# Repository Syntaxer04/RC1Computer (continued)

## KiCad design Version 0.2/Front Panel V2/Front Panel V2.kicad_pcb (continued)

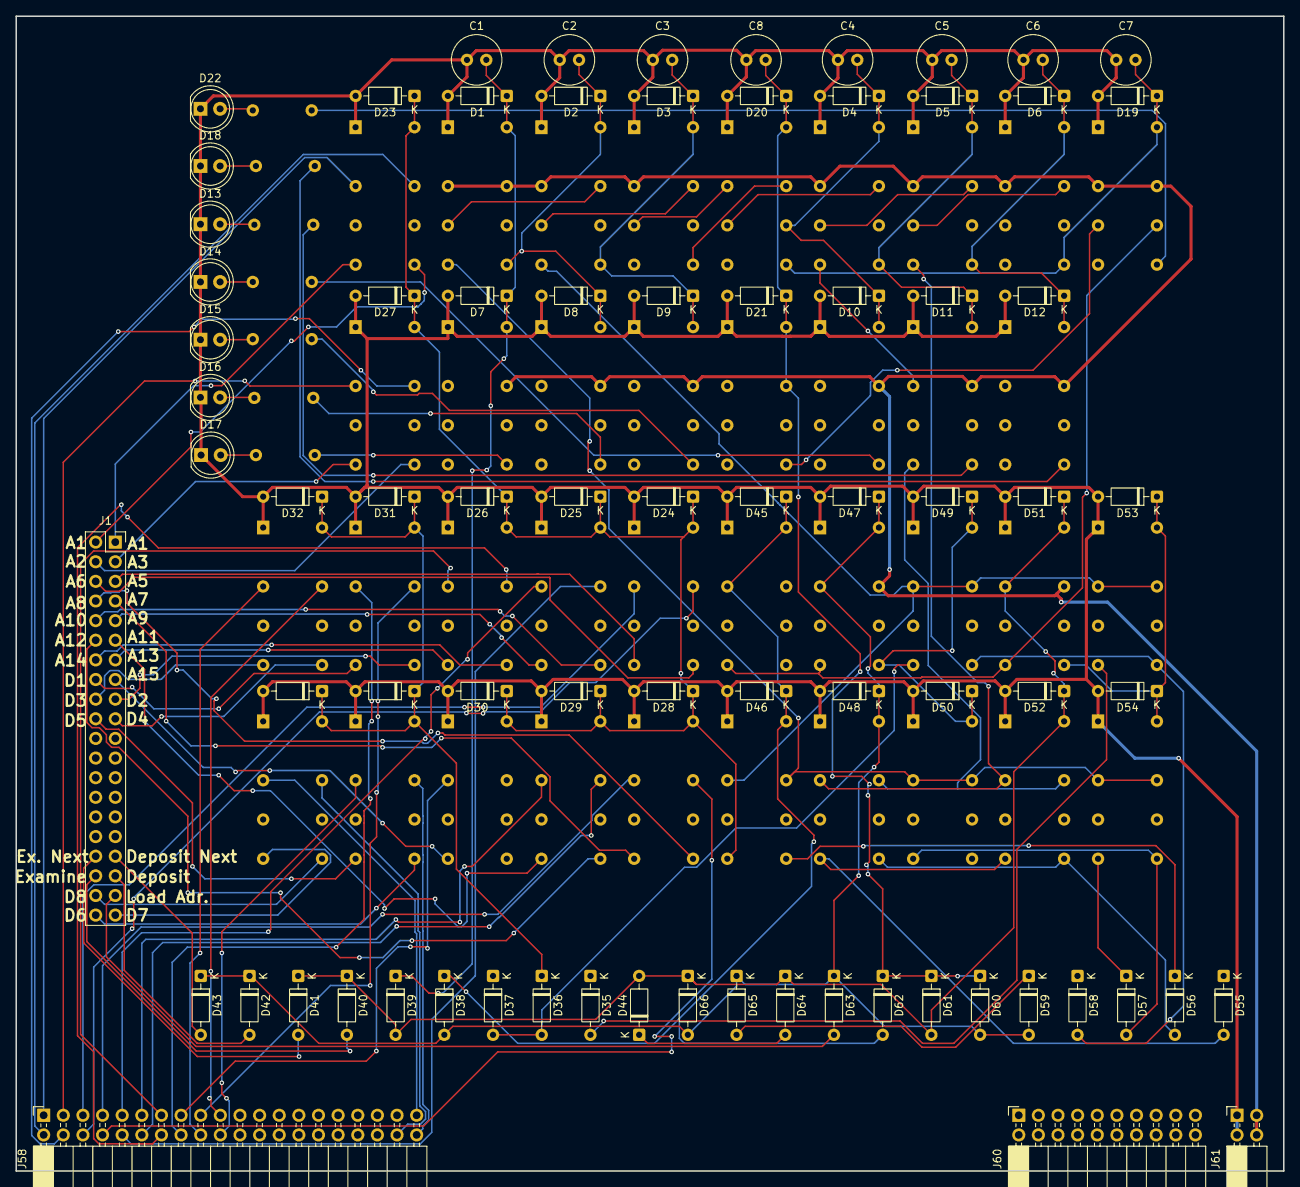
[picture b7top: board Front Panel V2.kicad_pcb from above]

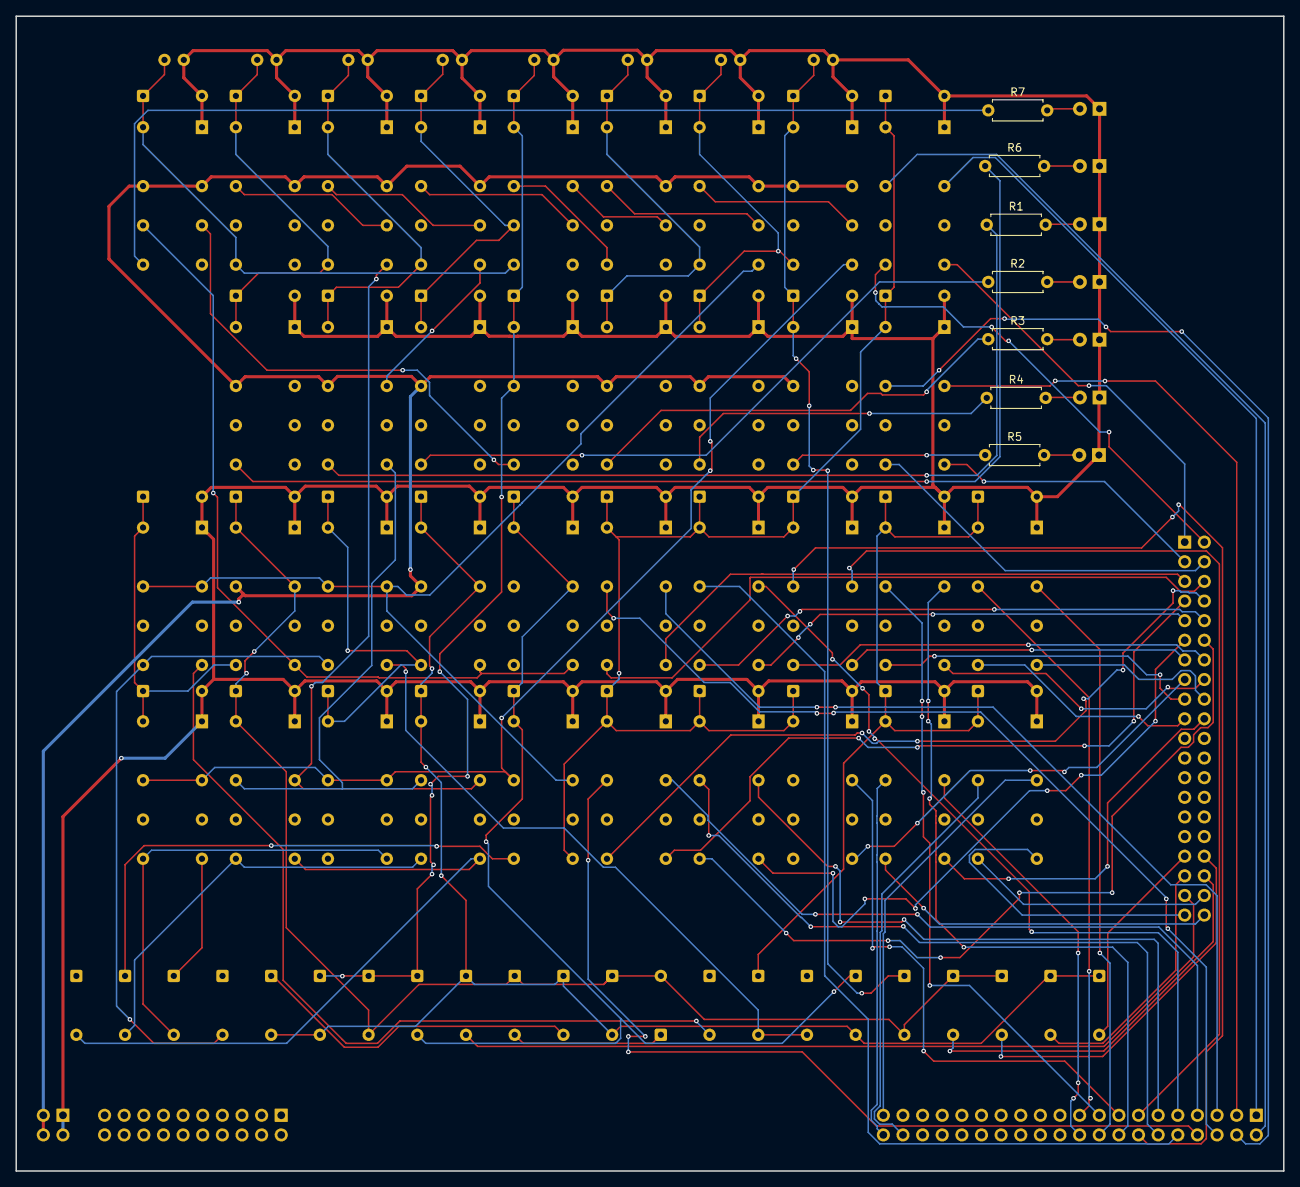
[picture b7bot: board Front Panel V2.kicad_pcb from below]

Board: 2 copper layers, 164.0 x 149.4 mm, 122 parts (7 on the bottom side), 106 nets.

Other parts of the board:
J60: Conn_02x10_Odd_Even; PinSocket_2x10_P2.54mm_Horizontal

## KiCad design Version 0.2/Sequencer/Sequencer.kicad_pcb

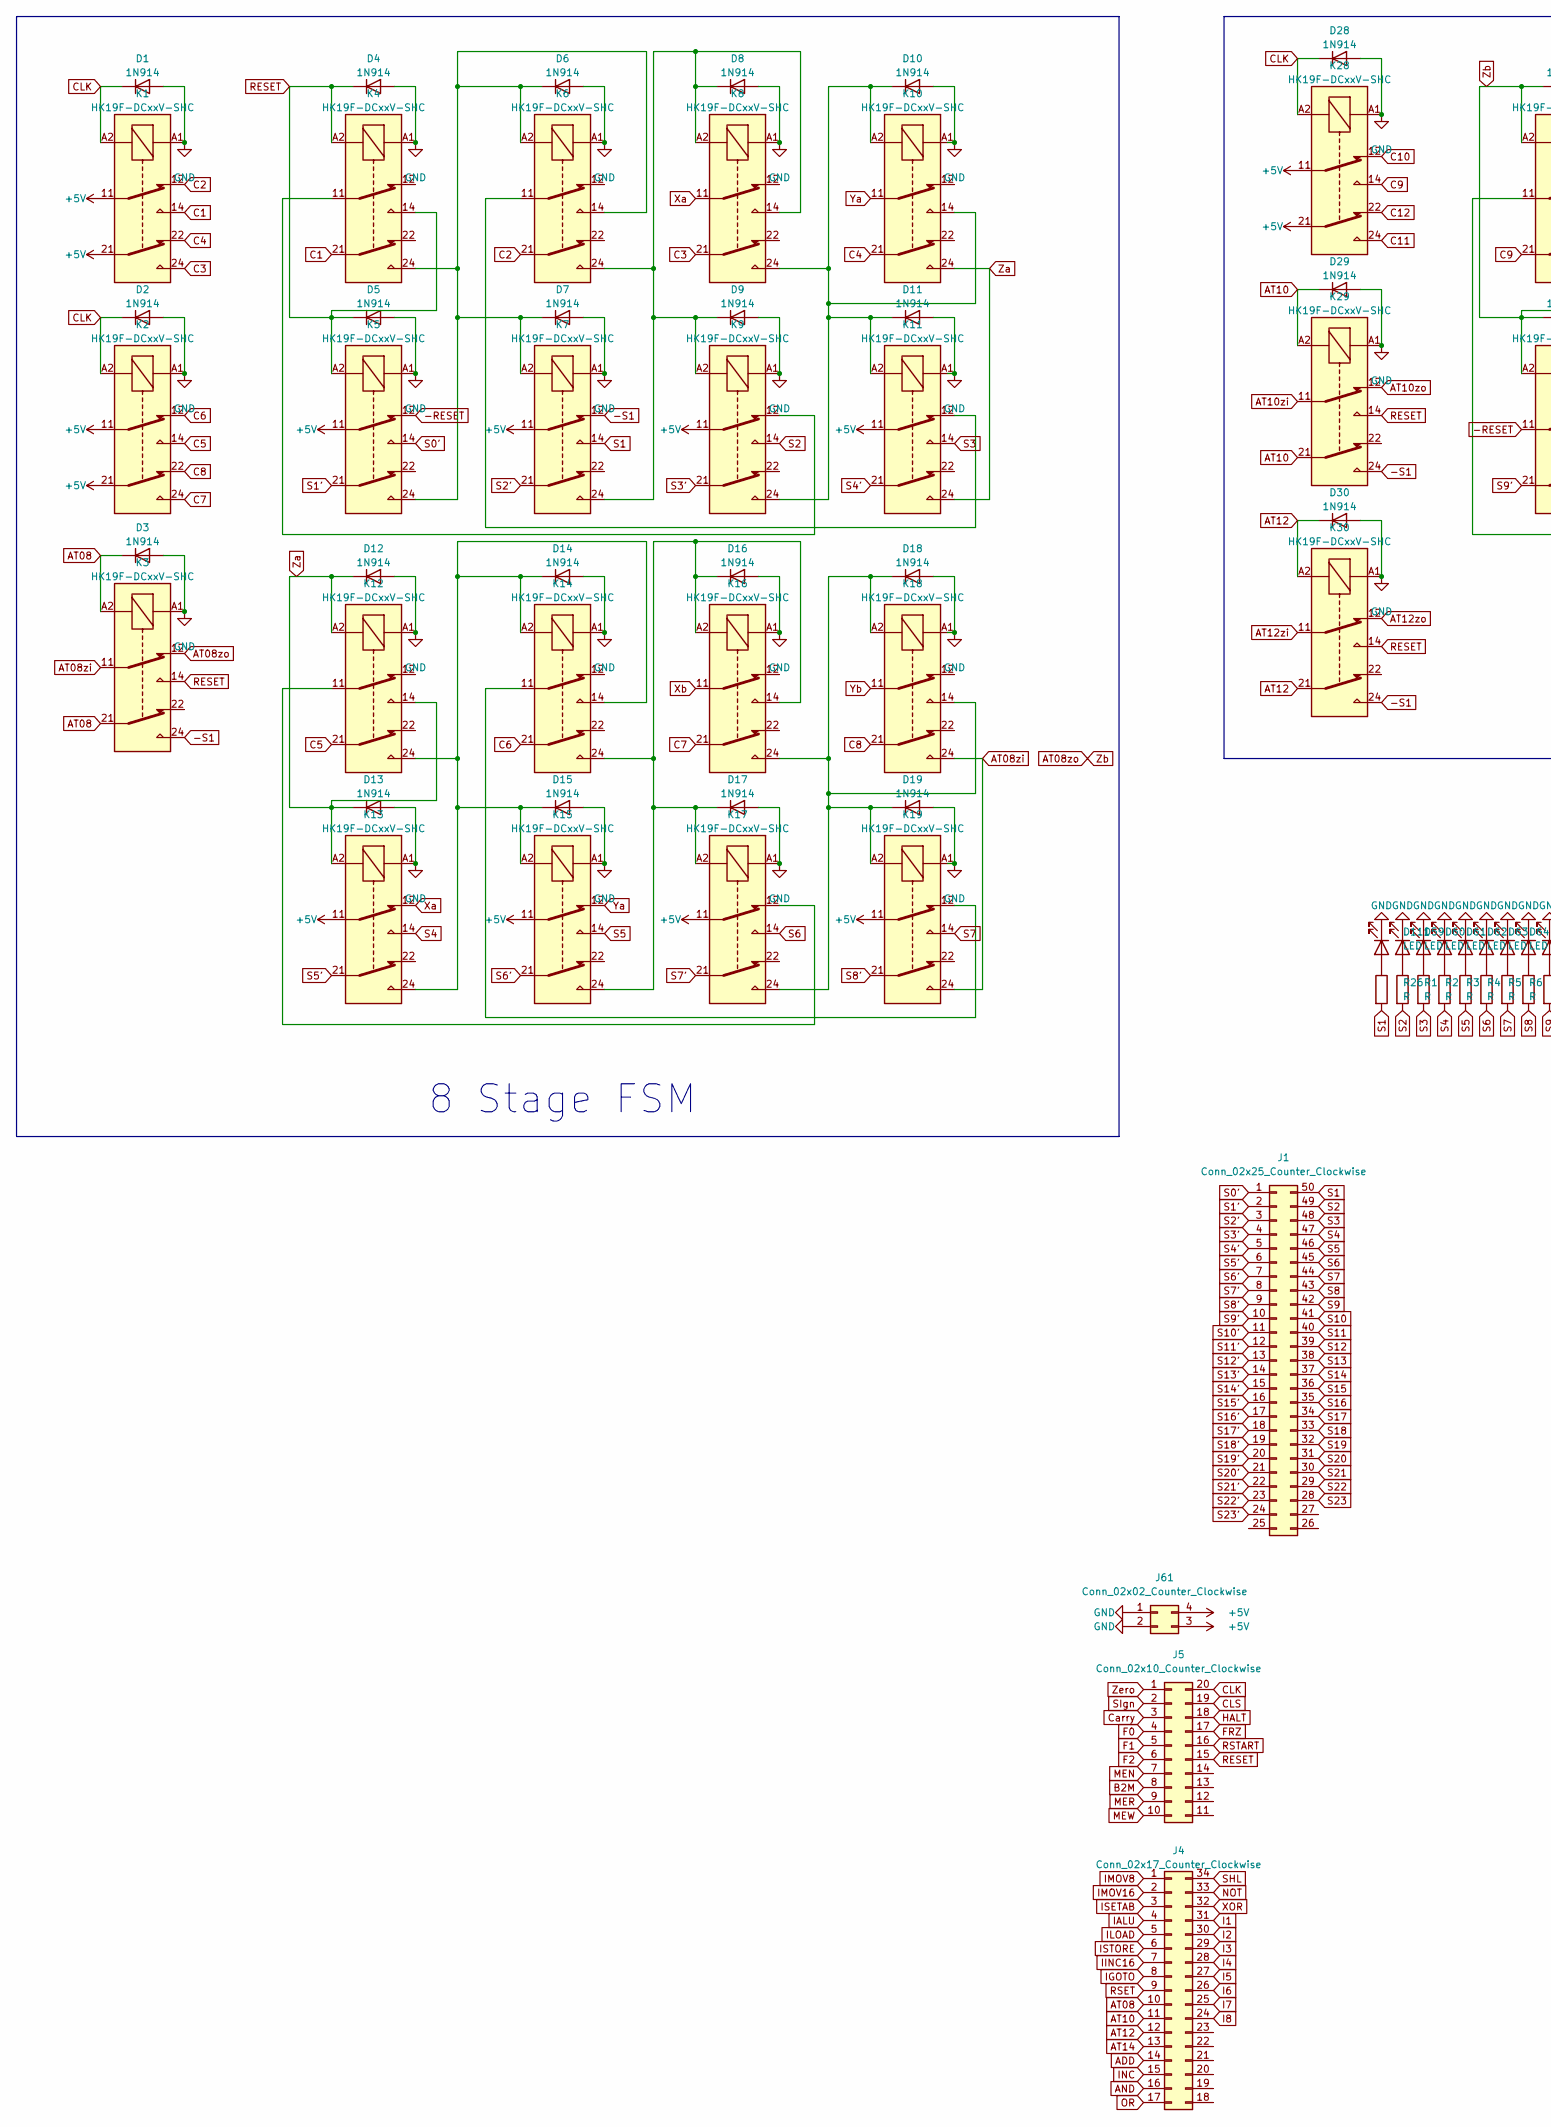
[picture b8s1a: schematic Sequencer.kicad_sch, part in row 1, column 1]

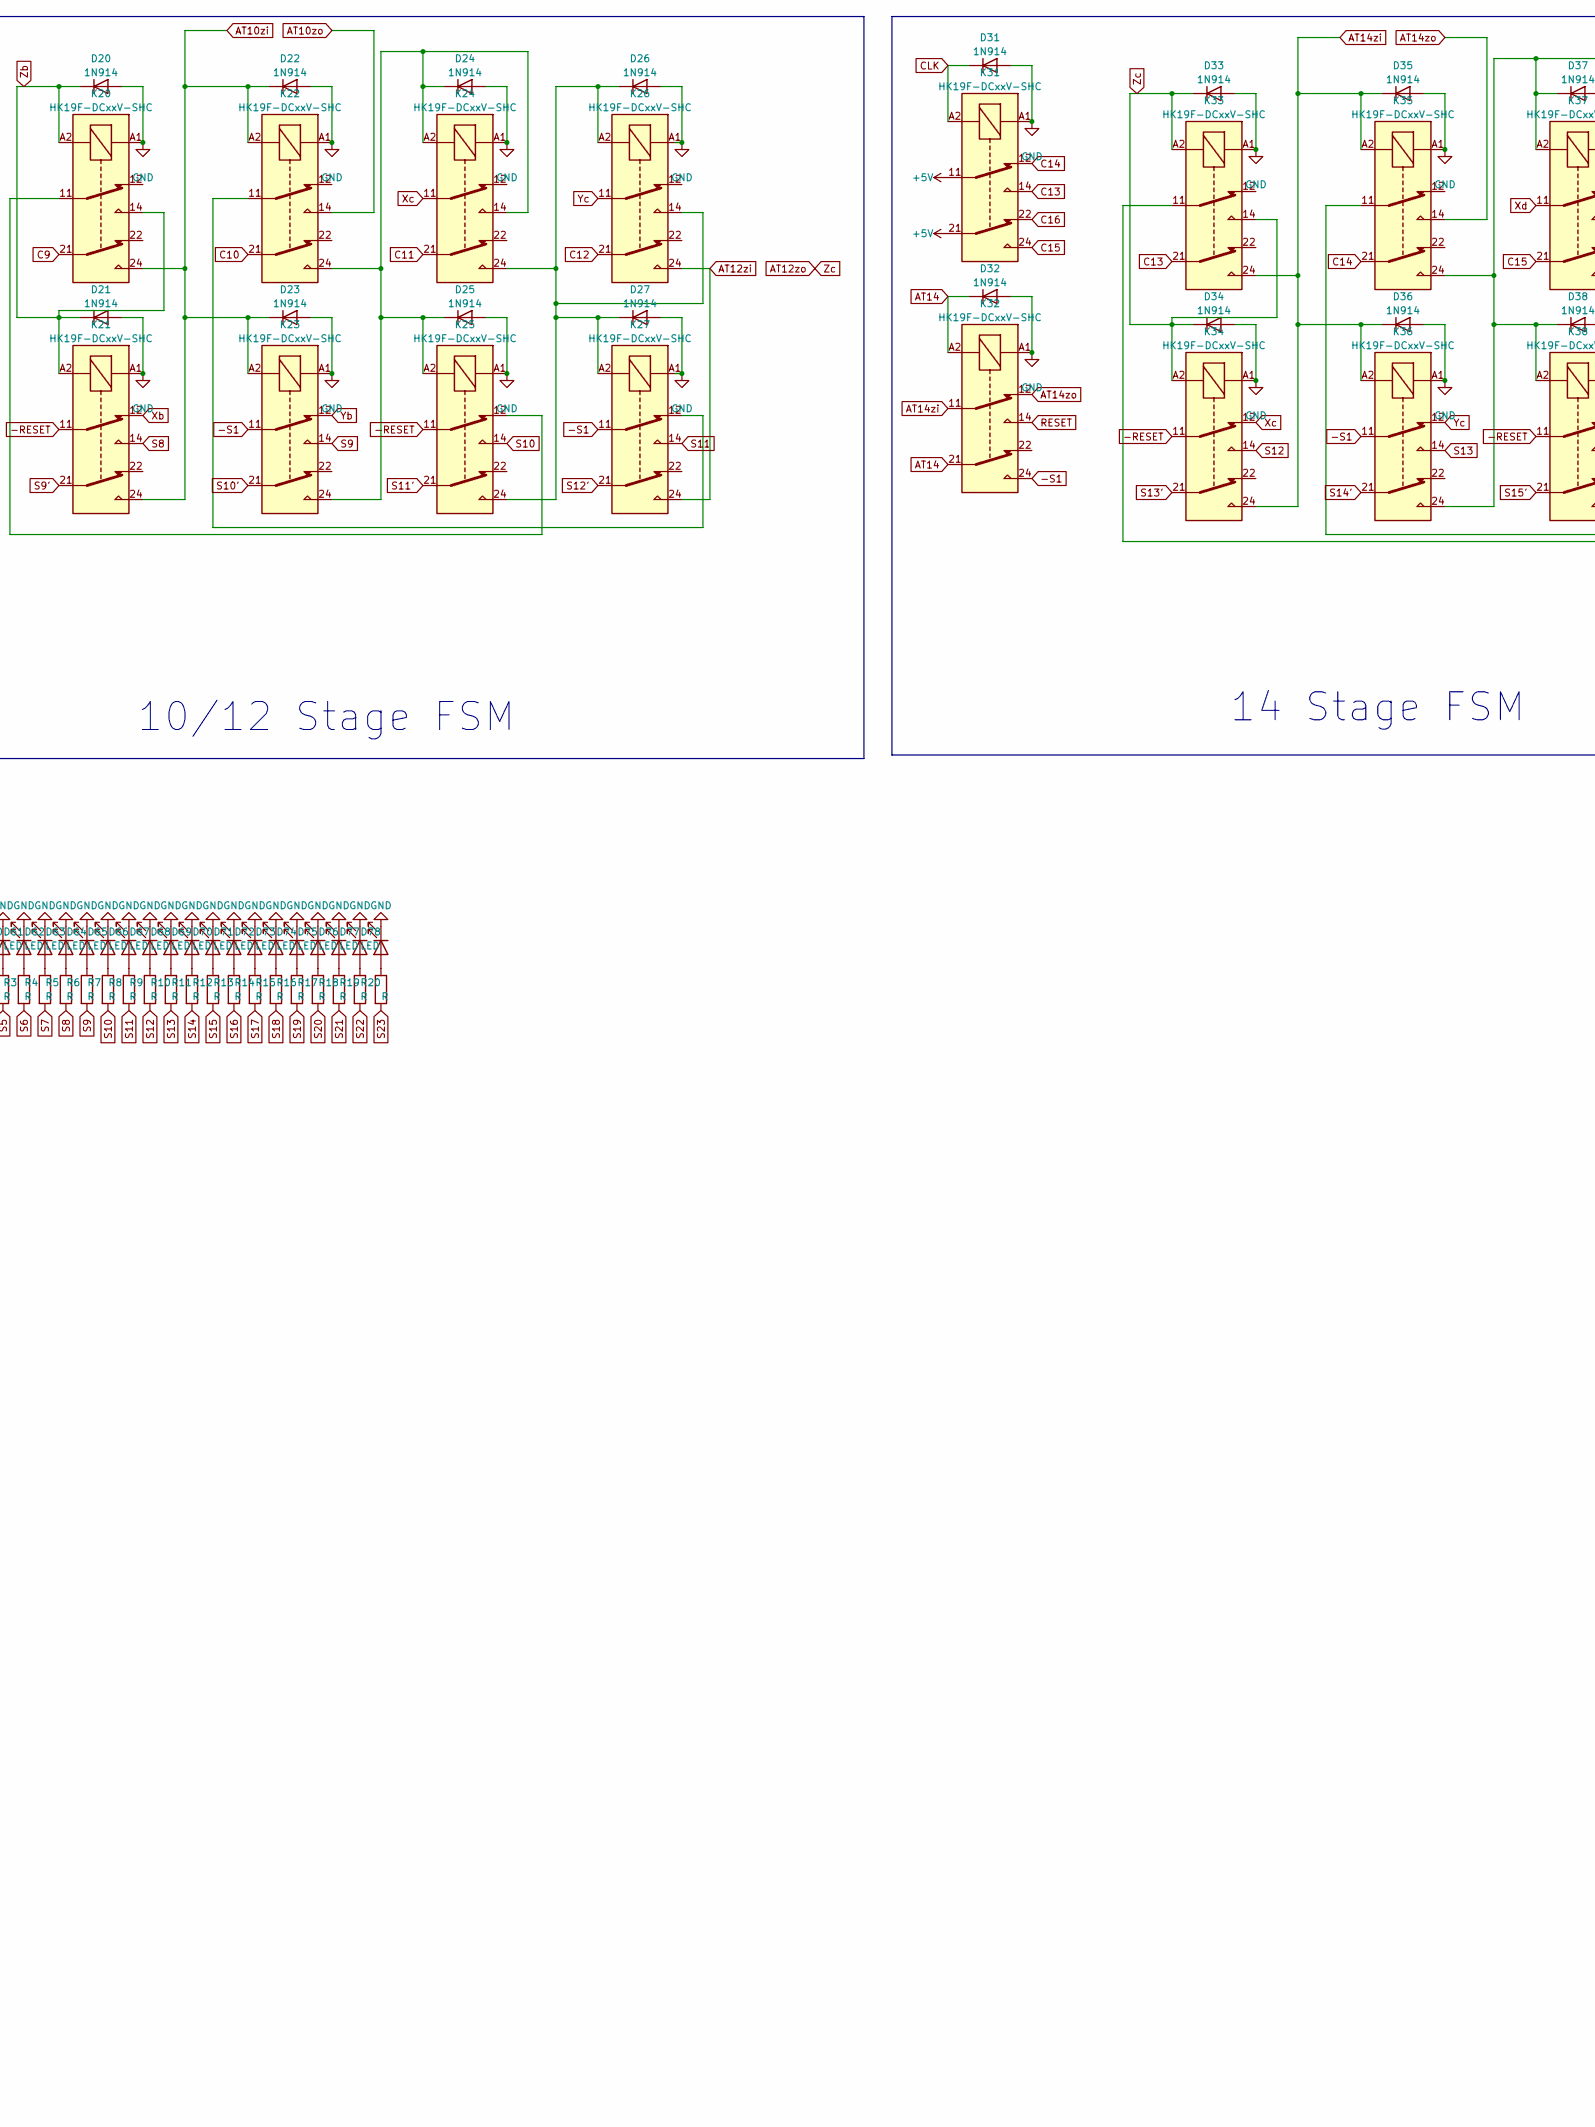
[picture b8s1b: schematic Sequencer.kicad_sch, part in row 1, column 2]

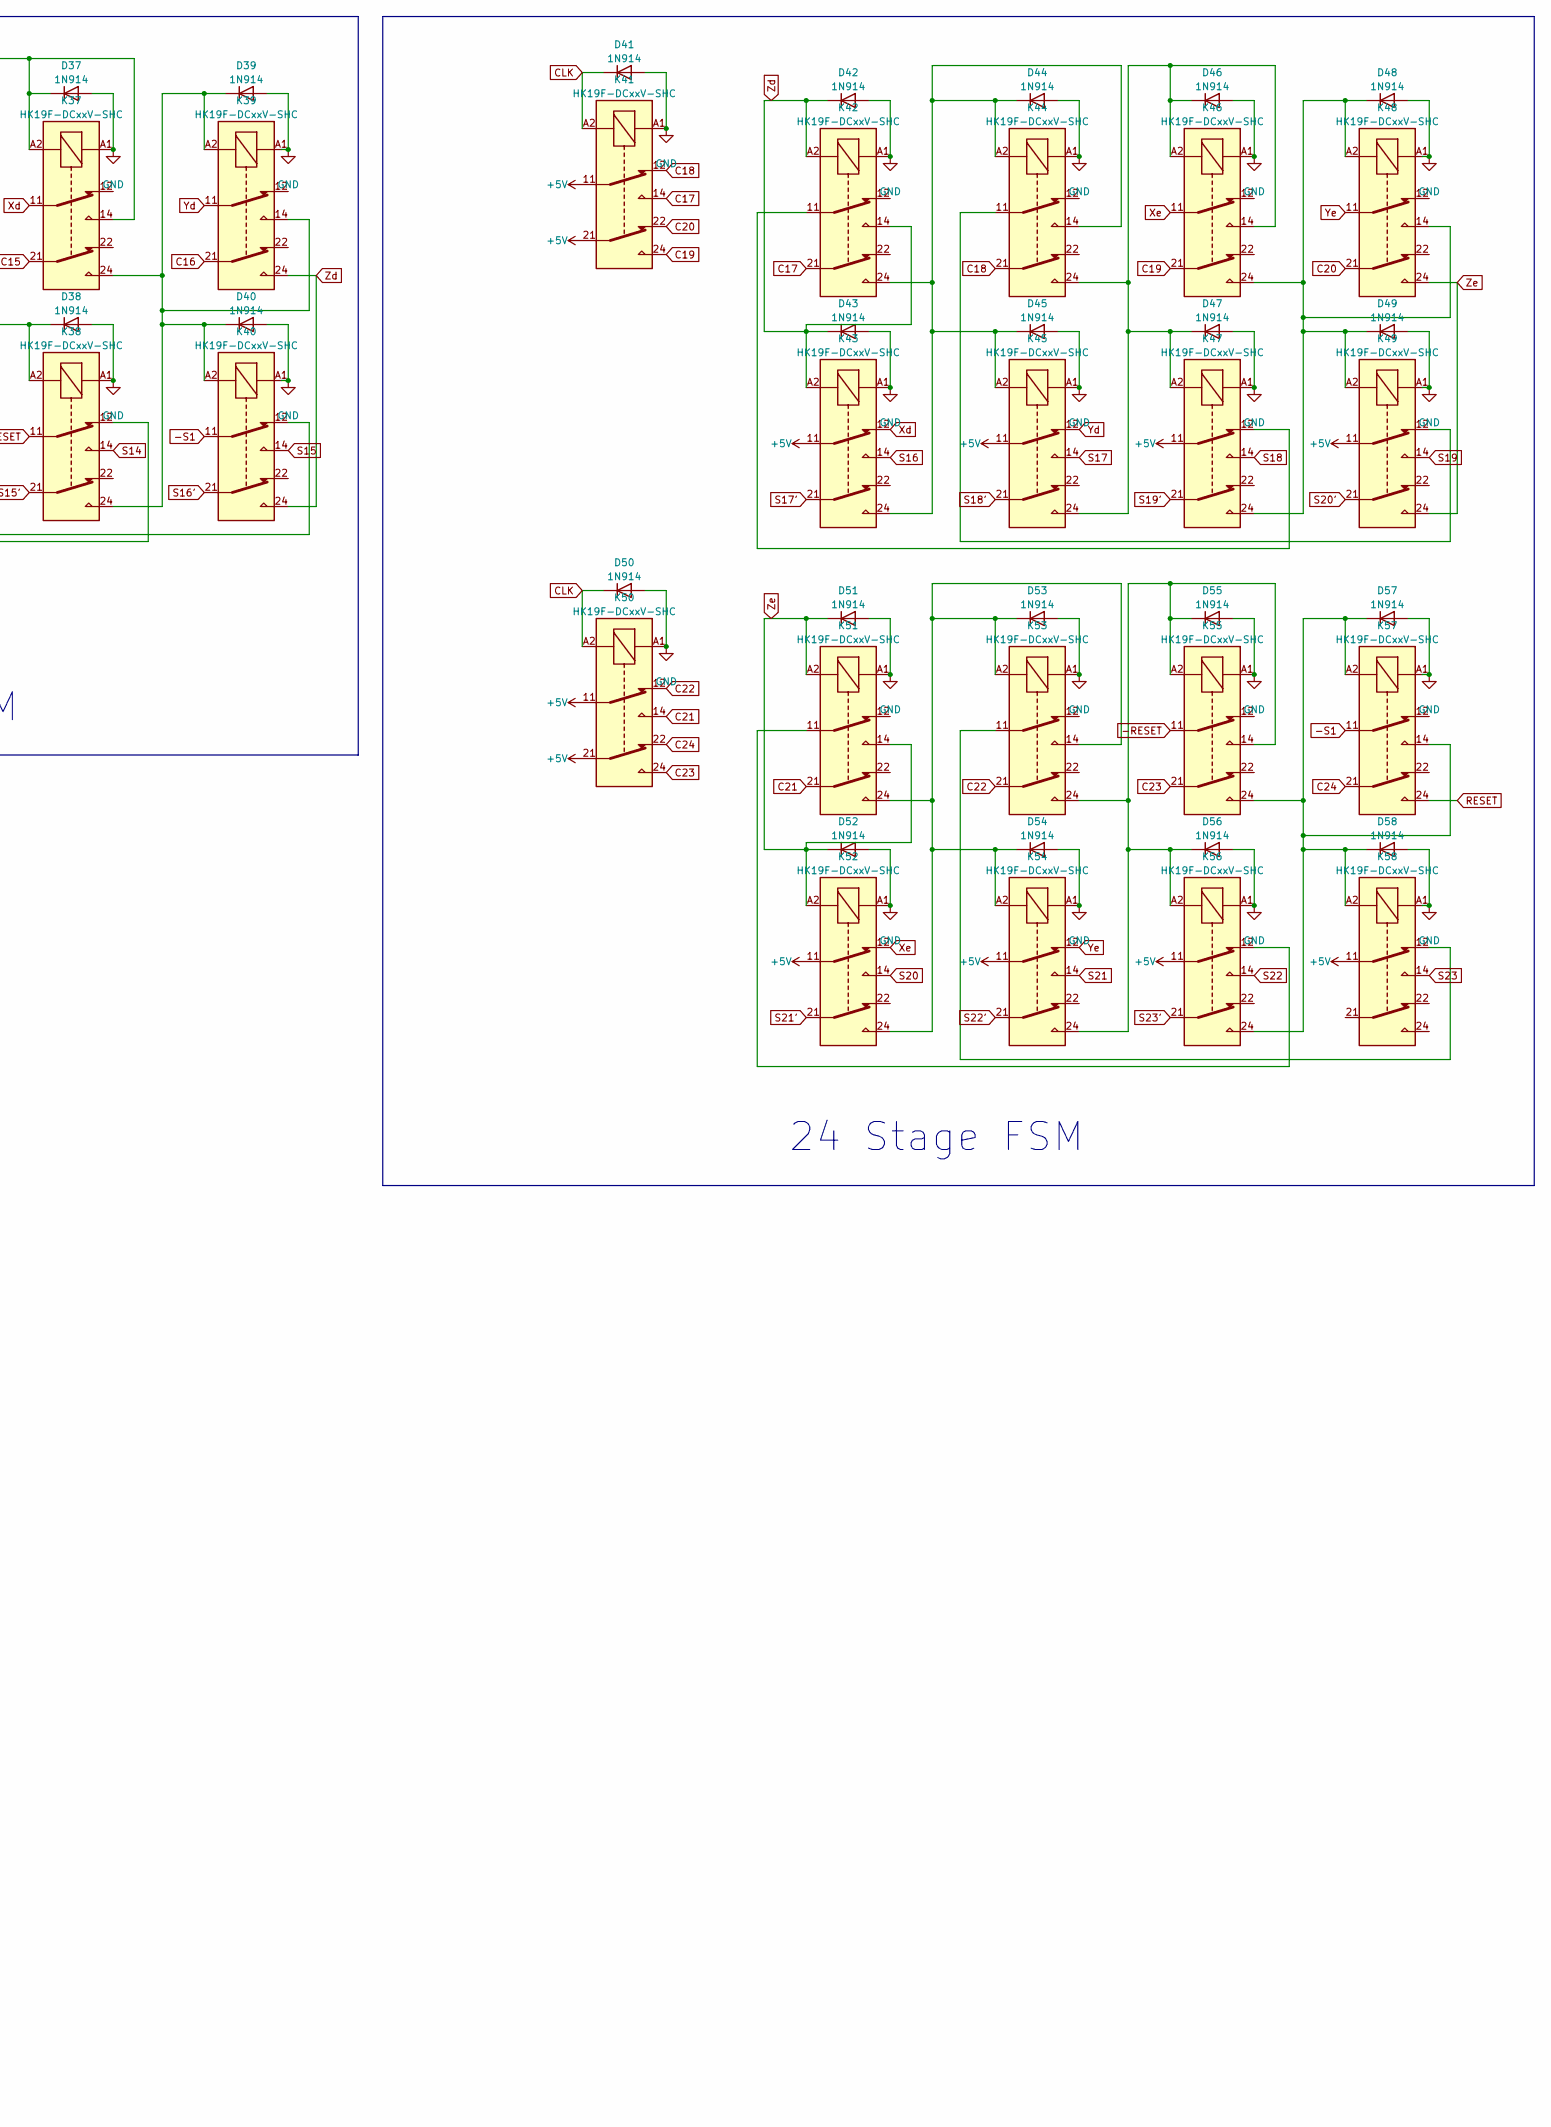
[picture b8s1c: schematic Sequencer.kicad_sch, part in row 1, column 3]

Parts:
D1, D2, D3, D4, D5, D6, D7, D8, D9, D10, D11, D12, D13, D14, D15, D16, D17, D18, D19, D20, D21, D22, D23, D24, D25, D26, D27, D28, D29, D30, D31, D32, D33, D34, D35, D36, D37, D38, D39, D40, D41, D42, D43, D44, D45, D46, D47, D48, D49, D50, D51, D52, D53, D54, D55, D56, D57, D58: 1N914; D_DO-35_SOD27_P7.62mm_Horizontal
D59, D60, D61, D62, D63, D64, D65, D66, D67, D68, D69, D70, D71, D72, D73, D74, D75, D76, D77, D78, D79, D80, D111: LED; LED_D5.0mm ohne SilkS
J1: Conn_02x25_Counter_Clockwise; PinSocket_2x25_P2.54mm_Horizontal
J4: Conn_02x17_Counter_Clockwise; PinSocket_2x17_P2.54mm_Horizontal
J5: Conn_02x10_Counter_Clockwise; PinSocket_2x10_P2.54mm_Horizontal
J61: Conn_02x02_Counter_Clockwise; PinSocket_2x02_P2.54mm_Horizontal
K1, K2, K3, K4, K5, K6, K7, K8, K9, K10, K11, K12, K13, K14, K15, K16, K17, K18, K19, K20, K21, K22, K23, K24, K25, K26, K27, K28, K29, K30, K31, K32, K33, K34, K35, K36, K37, K38, K39, K40, K41, K42, K43, K44, K45, K46, K47, K48, K49, K50, K51, K52, K53, K54, K55, K56, K57, K58: HK19F-DCxxV-SHC; Relay_DPDT_Finder_30.22 ohne SilkS
R1, R2, R3, R4, R5, R6, R7, R8, R9, R10, R11, R12, R13, R14, R15, R16, R17, R18, R19, R20, R21, R22, R26: R; R_Axial_DIN0204_L3.6mm_D1.6mm_P7.62mm_Horizontal

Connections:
+5V: J61.3, J61.4, K1.11, K1.21, K2.11, K2.21, K5.11, K7.11, K9.11, K11.11, K13.11, K15.11, K17.11, K19.11, K28.11, K28.21, K31.11, K31.21, K41.11, K41.21, K43.11, K45.11, K47.11, K49.11, K50.11, K50.21, K52.11, K54.11, K56.11, K58.11
-RESET: K5.12, K21.11, K25.11, K34.11, K38.11, K55.11
-S1: K3.24, K7.12, K23.11, K27.11, K29.24, K30.24, K32.24, K36.11, K40.11, K57.11
ADD: J4.14
AND: J4.16
AT08: D3.1 (K), J4.10, K3.21, K3.A2
AT08zi: K3.11, K18.24, K19.24
AT08zo: D20.1 (K), D21.1 (K), K3.12, K20.14, K20.A2, K21.A2
AT10: D29.1 (K), J4.11, K29.21, K29.A2
AT10zi: D22.1 (K), D23.1 (K), K20.24, K21.24, K22.A2, K23.A2, K29.11
AT10zo: K22.14, K29.12
AT12: D30.1 (K), J4.12, K30.21, K30.A2
AT12zi: K26.24, K27.24, K30.11
AT12zo: D33.1 (K), D34.1 (K), K30.12, K33.14, K33.A2, K34.A2
AT14: D32.1 (K), J4.13, K32.21, K32.A2
AT14zi: D35.1 (K), D36.1 (K), K32.11, K33.24, K34.24, K35.A2, K36.A2
AT14zo: K32.12, K35.14
B2M: J5.8
C1: K1.14, K4.21
C2: K1.12, K6.21
C3: K1.24, K8.21
C4: K1.22, K10.21
C5: K2.14, K12.21
C6: K2.12, K14.21
C7: K2.24, K16.21
C8: K2.22, K18.21
C9: K20.21, K28.14
C10: K22.21, K28.12
C11: K24.21, K28.24
C12: K26.21, K28.22
C13: K31.14, K33.21
C14: K31.12, K35.21
C15: K31.24, K37.21
C16: K31.22, K39.21
C17: K41.14, K42.21
C18: K41.12, K44.21
C19: K41.24, K46.21
C20: K41.22, K48.21
C21: K50.14, K51.21
C22: K50.12, K53.21
C23: K50.24, K55.21
C24: K50.22, K57.21
CLK: D1.1 (K), D2.1 (K), D28.1 (K), D31.1 (K), D41.1 (K), D50.1 (K), J5.20, K1.A2, K2.A2, K28.A2, K31.A2, K41.A2, K50.A2
CLS: J5.19
Carry: J5.3
F0: J5.4
F1: J5.5
F2: J5.6
FRZ: J5.17
GND: D1.2 (A), D2.2 (A), D3.2 (A), D4.2 (A), D5.2 (A), D6.2 (A), D7.2 (A), D8.2 (A), D9.2 (A), D10.2 (A), D11.2 (A), D12.2 (A), D13.2 (A), D14.2 (A), D15.2 (A), D16.2 (A), D17.2 (A), D18.2 (A), D19.2 (A), D20.2 (A), D21.2 (A), D22.2 (A), D23.2 (A), D24.2 (A), D25.2 (A), D26.2 (A), D27.2 (A), D28.2 (A), D29.2 (A), D30.2 (A), D31.2 (A), D32.2 (A), D33.2 (A), D34.2 (A), D35.2 (A), D36.2 (A), D37.2 (A), D38.2 (A), D39.2 (A), D40.2 (A), D41.2 (A), D42.2 (A), D43.2 (A), D44.2 (A), D45.2 (A), D46.2 (A), D47.2 (A), D48.2 (A), D49.2 (A), D50.2 (A), D51.2 (A), D52.2 (A), D53.2 (A), D54.2 (A), D55.2 (A), D56.2 (A), D57.2 (A), D58.2 (A), D59.1 (K), D60.1 (K), D61.1 (K), D62.1 (K), D63.1 (K), D64.1 (K), D65.1 (K), D66.1 (K), D67.1 (K), D68.1 (K), D69.1 (K), D70.1 (K), D71.1 (K), D72.1 (K), D73.1 (K), D74.1 (K), D75.1 (K), D76.1 (K), D77.1 (K), D78.1 (K), D79.1 (K), D80.1 (K), D111.1 (K), J61.1, J61.2, K1.A1, K2.A1, K3.A1, K4.A1, K5.A1, K6.A1, K7.A1, K8.A1, K9.A1, K10.A1, K11.A1, K12.A1, K13.A1, K14.A1, K15.A1, K16.A1, K17.A1, K18.A1, K19.A1, K20.A1, K21.A1, K22.A1, K23.A1, K24.A1, K25.A1, K26.A1, K27.A1, K28.A1, K29.A1, K30.A1, K31.A1, K32.A1, K33.A1, K34.A1, K35.A1, K36.A1, K37.A1, K38.A1, K39.A1, K40.A1, K41.A1, K42.A1, K43.A1, K44.A1, K45.A1, K46.A1, K47.A1, K48.A1, K49.A1, K50.A1, K51.A1, K52.A1, K53.A1, K54.A1, K55.A1, K56.A1, K57.A1, K58.A1
HALT: J5.18
I1: J4.31
I2: J4.30
I3: J4.29
I4: J4.28
I5: J4.27
I6: J4.26
I7: J4.25
I8: J4.24
IALU: J4.4
IGOTO: J4.8
IINC16: J4.7
ILOAD: J4.5
IMOV8: J4.1
IMOV16: J4.2
INC: J4.15
ISETAB: J4.3
ISTORE: J4.6
MEN: J5.7
MER: J5.9
MEW: J5.10
NOT: J4.33
unnamed: D6.1 (K), D7.1 (K), K4.24, K5.24, K6.14, K6.A2, K7.A2
unnamed: D8.1 (K), D9.1 (K), K6.24, K7.24, K8.14, K8.A2, K9.A2
unnamed: D10.1 (K), D11.1 (K), K8.24, K9.24, K10.14, K10.A2, K11.A2
unnamed: D14.1 (K), D15.1 (K), K12.24, K13.24, K14.14, K14.A2, K15.A2
unnamed: D16.1 (K), D17.1 (K), K14.24, K15.24, K16.14, K16.A2, K17.A2
unnamed: D18.1 (K), D19.1 (K), K16.24, K17.24, K18.14, K18.A2, K19.A2
unnamed: D24.1 (K), D25.1 (K), K22.24, K23.24, K24.14, K24.A2, K25.A2
unnamed: D26.1 (K), D27.1 (K), K24.24, K25.24, K26.14, K26.A2, K27.A2
unnamed: D37.1 (K), D38.1 (K), K35.24, K36.24, K37.14, K37.A2, K38.A2
unnamed: D39.1 (K), D40.1 (K), K37.24, K38.24, K39.14, K39.A2, K40.A2
unnamed: D44.1 (K), D45.1 (K), K42.24, K43.24, K44.14, K44.A2, K45.A2
unnamed: D46.1 (K), D47.1 (K), K44.24, K45.24, K46.14, K46.A2, K47.A2
unnamed: D48.1 (K), D49.1 (K), K46.24, K47.24, K48.14, K48.A2, K49.A2
unnamed: D53.1 (K), D54.1 (K), K51.24, K52.24, K53.14, K53.A2, K54.A2
unnamed: D55.1 (K), D56.1 (K), K53.24, K54.24, K55.14, K55.A2, K56.A2
unnamed: D57.1 (K), D58.1 (K), K55.24, K56.24, K57.14, K57.A2, K58.A2
unnamed: D59.2 (A), R1.1
unnamed: D60.2 (A), R2.1
unnamed: D61.2 (A), R3.1
unnamed: D62.2 (A), R4.1
unnamed: D63.2 (A), R5.1
unnamed: D64.2 (A), R6.1
unnamed: D65.2 (A), R7.1
unnamed: D66.2 (A), R8.1
unnamed: D67.2 (A), R9.1
unnamed: D68.2 (A), R10.1
unnamed: D69.2 (A), R11.1
unnamed: D70.2 (A), R12.1
unnamed: D71.2 (A), R13.1
unnamed: D72.2 (A), R14.1
unnamed: D73.2 (A), R15.1
unnamed: D74.2 (A), R16.1
unnamed: D75.2 (A), R17.1
unnamed: D76.2 (A), R18.1
unnamed: D77.2 (A), R19.1
unnamed: D78.2 (A), R20.1
unnamed: D79.2 (A), R21.1
unnamed: D80.2 (A), R22.1
unnamed: D111.2 (A), R26.1
unnamed: K4.11, K9.12
unnamed: K6.11, K11.12
unnamed: K12.11, K17.12
unnamed: K14.11, K19.12
unnamed: K20.11, K25.12
unnamed: K22.11, K27.12
unnamed: K33.11, K38.12
unnamed: K35.11, K40.12
unnamed: K42.11, K47.12
unnamed: K44.11, K49.12
unnamed: K51.11, K56.12
unnamed: K53.11, K58.12
OR: J4.17
RESET: D4.1 (K), D5.1 (K), J5.15, K3.14, K4.14, K4.A2, K5.A2, K29.14, K30.14, K32.14, K57.24
RSET: J4.9
RSTART: J5.16
S0': J1.1, K5.14
S1: J1.50, K7.14, R26.2
S1': J1.2, K5.21
S2: J1.49, K9.14, R1.2
S2': J1.3, K7.21
S3: J1.48, K11.14, R2.2
S3': J1.4, K9.21
S4: J1.47, K13.14, R3.2
S4': J1.5, K11.21
S5: J1.46, K15.14, R4.2
S5': J1.6, K13.21
S6: J1.45, K17.14, R5.2
S6': J1.7, K15.21
S7: J1.44, K19.14, R6.2
S7': J1.8, K17.21
S8: J1.43, K21.14, R7.2
S8': J1.9, K19.21
S9: J1.42, K23.14, R8.2
S9': J1.10, K21.21
S10: J1.41, K25.14, R9.2
S10': J1.11, K23.21
S11: J1.40, K27.14, R10.2
S11': J1.12, K25.21
S12: J1.39, K34.14, R11.2
S12': J1.13, K27.21
S13: J1.38, K36.14, R12.2
S13': J1.14, K34.21
S14: J1.37, K38.14, R13.2
S14': J1.15, K36.21
S15: J1.36, K40.14, R14.2
S15': J1.16, K38.21
S16: J1.35, K43.14, R15.2
S16': J1.17, K40.21
S17: J1.34, K45.14, R16.2
S17': J1.18, K43.21
S18: J1.33, K47.14, R17.2
S18': J1.19, K45.21
S19: J1.32, K49.14, R18.2
S19': J1.20, K47.21
S20: J1.31, K52.14, R19.2
S20': J1.21, K49.21
S21: J1.30, K54.14, R20.2
S21': J1.22, K52.21
S22: J1.29, K56.14, R21.2
S22': J1.23, K54.21
S23: J1.28, K58.14, R22.2
S23': J1.24, K56.21
SHL: J4.34
SIgn: J5.2
XOR: J4.32
Xa: K8.11, K13.12
Xb: K16.11, K21.12
Xc: K24.11, K34.12
Xd: K37.11, K43.12
Xe: K46.11, K52.12
Ya: K10.11, K15.12
Yb: K18.11, K23.12
Yc: K26.11, K36.12
Yd: K39.11, K45.12
Ye: K48.11, K54.12
Za: D12.1 (K), D13.1 (K), K10.24, K11.24, K12.14, K12.A2, K13.A2
Zd: D42.1 (K), D43.1 (K), K39.24, K40.24, K42.14, K42.A2, K43.A2
Ze: D51.1 (K), D52.1 (K), K48.24, K49.24, K51.14, K51.A2, K52.A2
Zero: J5.1

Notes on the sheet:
14 Stage FSM
10/12 Stage FSM
8 Stage FSM
24 Stage FSM

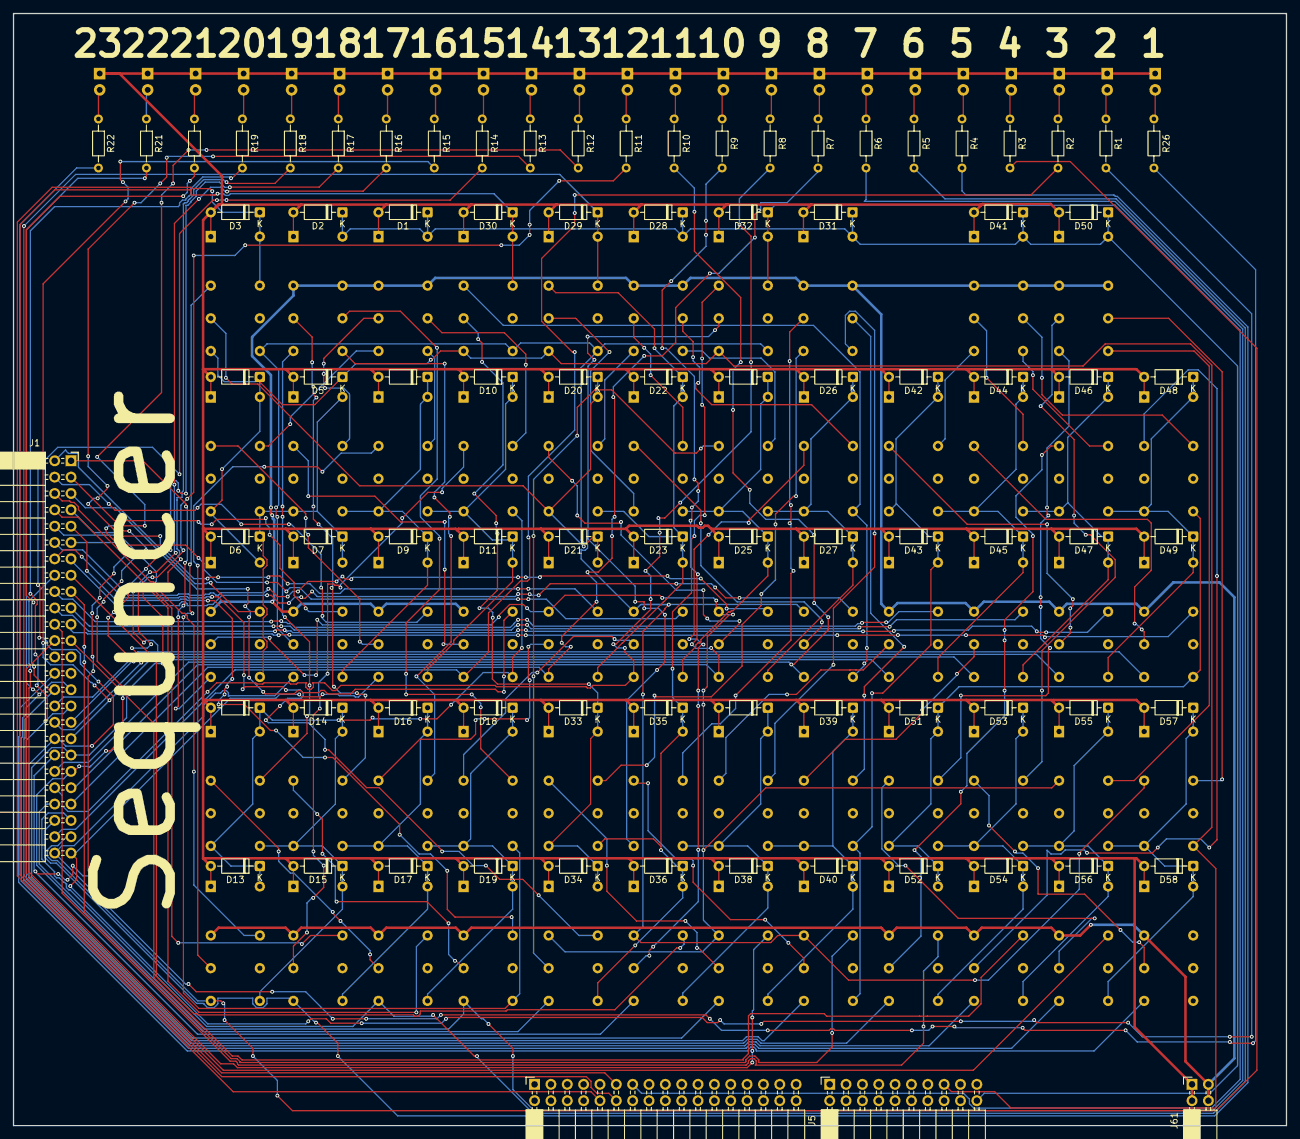
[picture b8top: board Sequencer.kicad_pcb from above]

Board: 2 copper layers, 197.8 x 172.8 mm, 166 parts (0 on the bottom side), 153 nets.

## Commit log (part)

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2025-06-25 Update README.md: Typo
2026-01-20 Second Version, overall improvements.
    Added Tape Loader and Front Panel Function Board aswell
2026-06-26 Mostly complete version of the RC-1 made in ttl
    Version of the Computer made out of TTL Chips. Should be compatible with the relay version, although not tested yet.
